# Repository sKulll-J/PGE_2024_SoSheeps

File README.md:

# PGE_2024_SoSheeps
Ce GitHub servira dans une première partie à regrouper les documentations, ressources utiles et notes en tous genres pour le PGE des SME 2024.

On sépareras les ressources dans des dossiers différents.

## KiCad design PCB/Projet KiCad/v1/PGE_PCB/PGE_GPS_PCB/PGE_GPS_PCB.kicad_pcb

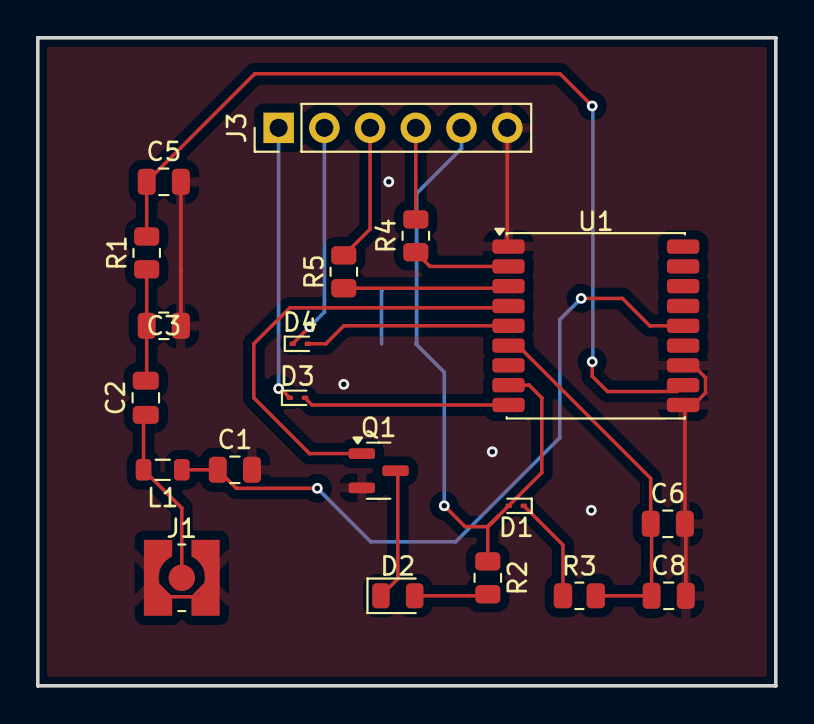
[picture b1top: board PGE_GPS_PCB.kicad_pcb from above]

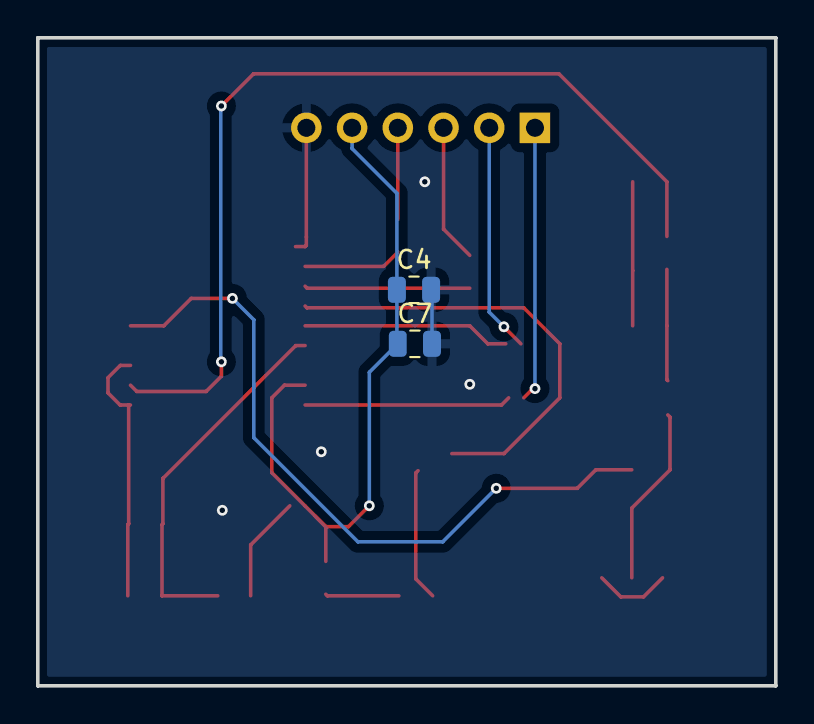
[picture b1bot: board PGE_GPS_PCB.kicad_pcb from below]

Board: 2 copper layers, 41.0 x 36.0 mm, 22 parts (2 on the bottom side), 19 nets.

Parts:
C1, C7, C8: 100nF; C_0805_2012Metric
C2: 100pF; C_0805_2012Metric
C3, C5: DNP_0805; C_0805_2012Metric
C4, C6: 4.7µF; C_0805_2012Metric
D1, D3, D4: RB521CM-30; D_SOD-923
D2: LED; LED_0805_2012Metric
J1: Antenne_GPS; WR-MMCX_Wuerth_66012102111404_Vertical
J3: Conn_01x06_Pin; PinHeader_1x06_P2.54mm_Vertical
L1: 47nH; L_0805_2012Metric
Q1: IRLML6244; SOT-23
R1: 0R; R_0805_2012Metric
R2: 330R; R_0805_2012Metric
R3: 1K; R_0805_2012Metric
R4, R5: 100R; R_0805_2012Metric
U1: L76-R; Quectel_L76

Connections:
1PPS: Q1.1 (G), U1.4 (1PPS)
GND: C1.2, C3.2, C4.2, C5.2, C6.2, C7.2, C8.2, J1.2 (Ext), J3.6, Q1.2 (S), U1.1 (GND), U1.10 (GND), U1.12 (GND)
GPS_RX: J3.3, R5.2
GPS_TX: J3.4, R4.2
GPS_reset: D3.1, J3.1
unnamed: C2.2, C3.1, R1.1
unnamed: D1.1, R3.1
unnamed: D2.2 (A), R2.2
unnamed: D2.1 (K), Q1.3 (D)
unnamed: D3.2 (A), U1.9 (~RESET)
unnamed: D4.2 (A), U1.5 (STANDBY)
unnamed: C2.1, J1.1 (In), L1.2
unnamed: R5.1, U1.3 (RXD1)
unnamed: R4.1, U1.2 (TXD1)
RF_IN: C5.1, R1.2, U1.11 (RF_IN)
VCC_RF: C1.1, L1.1, U1.14 (VCC_RF)
VDD_3.3V: C4.1, C7.1, D1.2 (A), J3.5, R2.1, U1.8 (VCC)
V_BCKP: C6.1, C8.1, R3.2, U1.6 (V_BCKP)
standby: D4.1, J3.2

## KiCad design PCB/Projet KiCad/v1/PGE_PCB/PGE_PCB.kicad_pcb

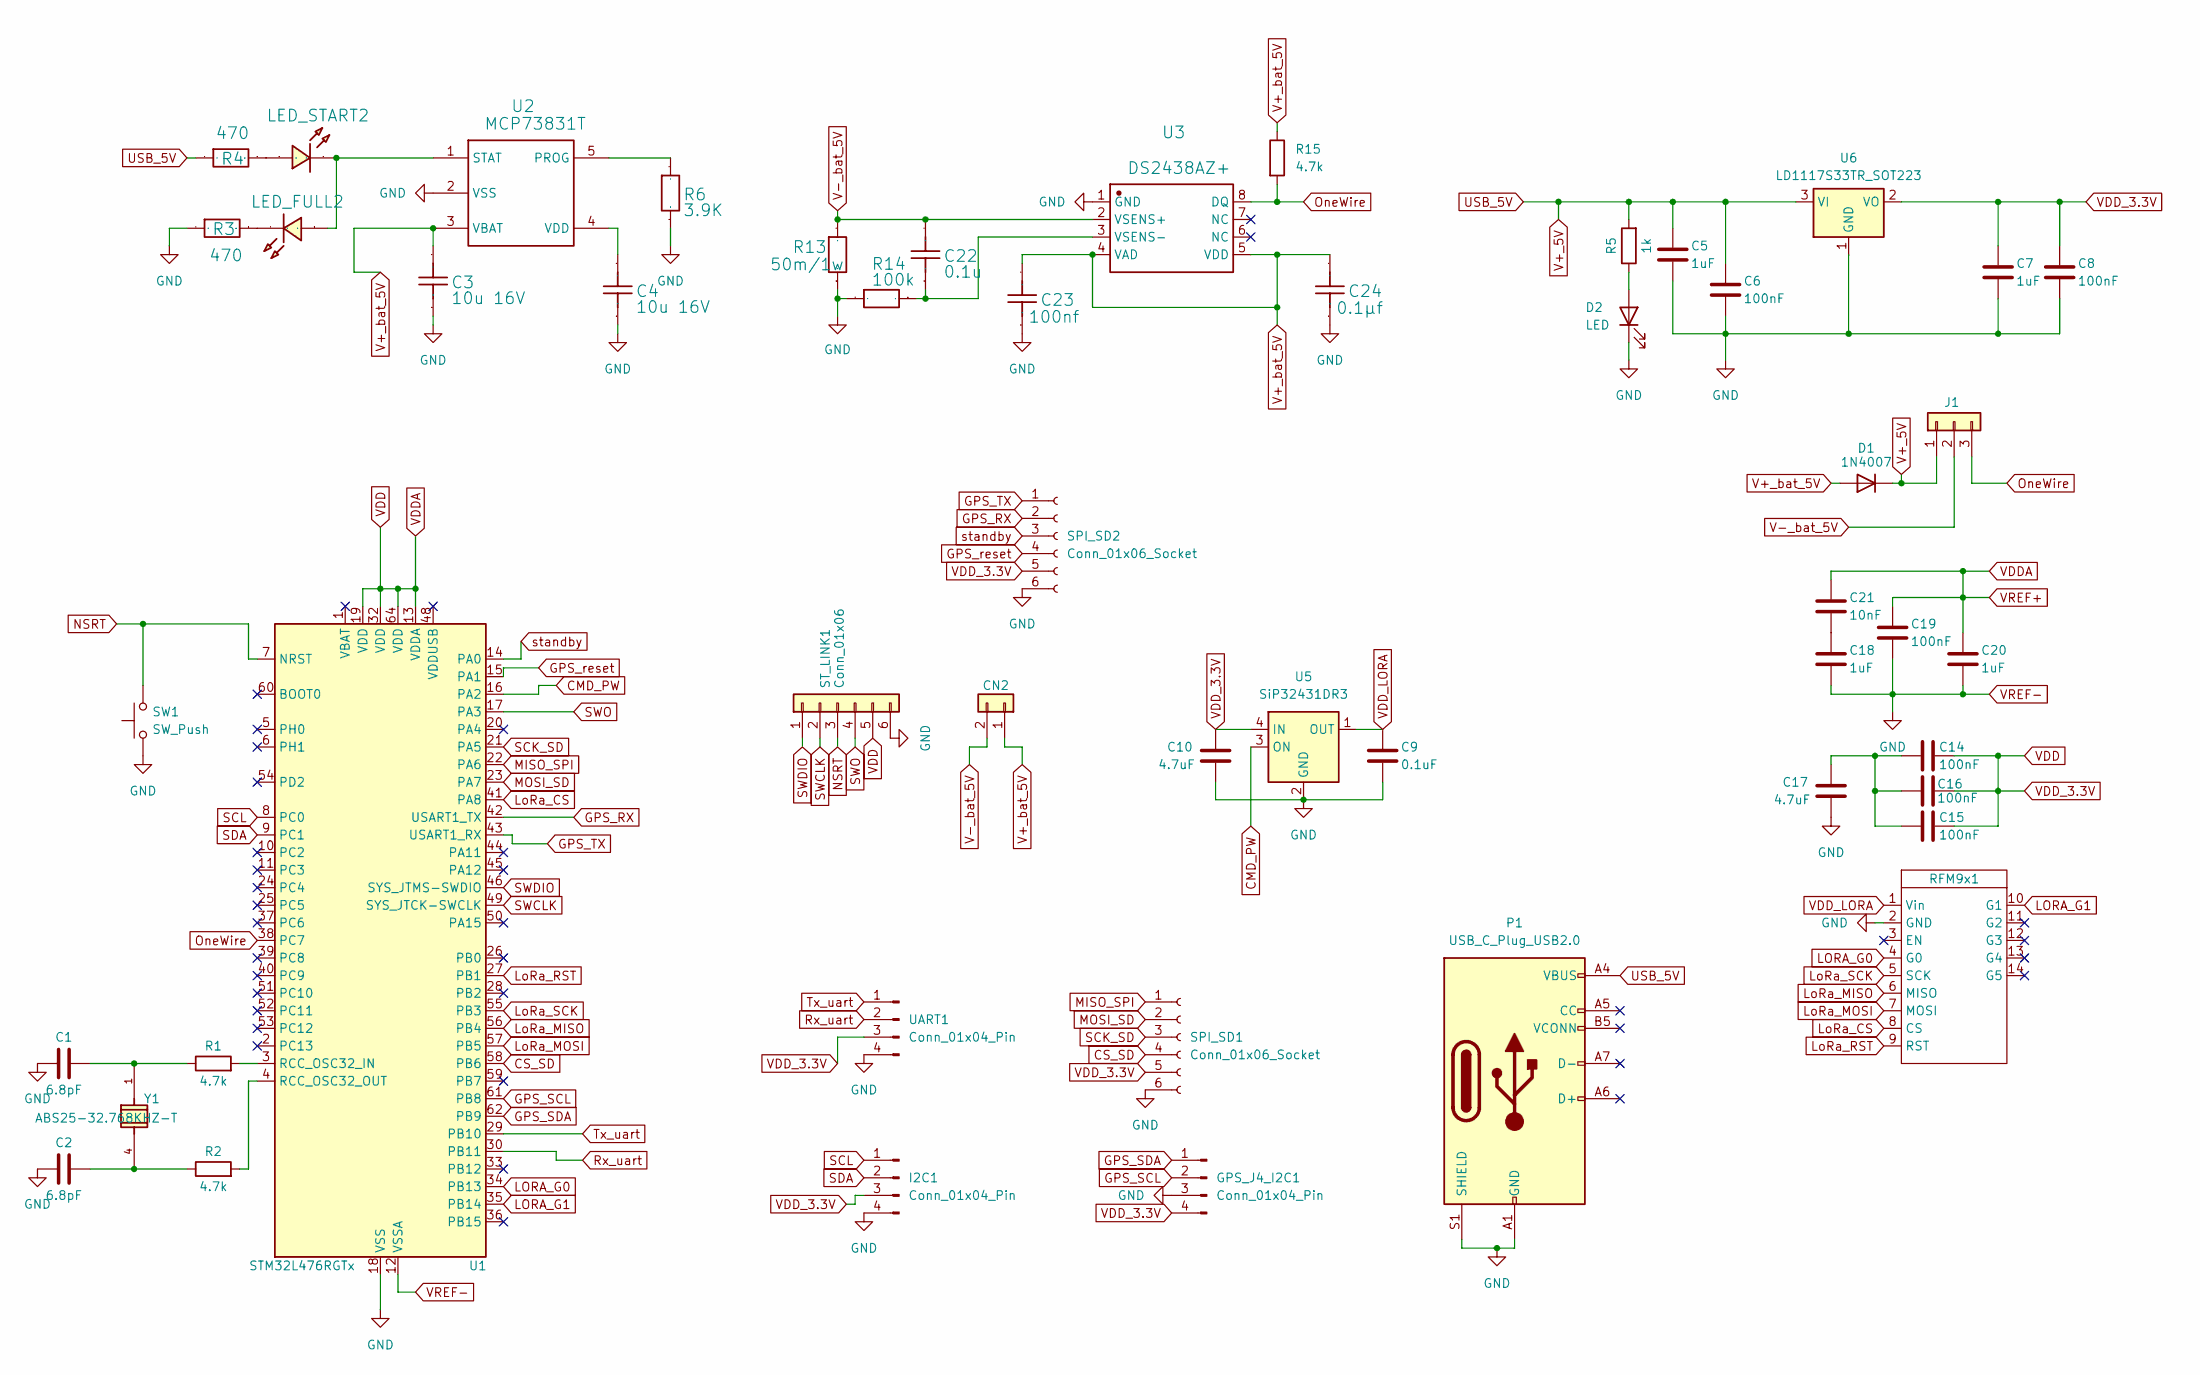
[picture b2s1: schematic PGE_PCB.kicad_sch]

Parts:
C1, C2: 6.8pF; C_0805_2012Metric
C3, C4: 10u 16V; C_0805_2012Metric
C5, C7, C18, C20: 1uF; C_0805_2012Metric
C6, C8, C14, C15, C16, C19: 100nF; C_0805_2012Metric
C9: 0.1uF; C_0805_2012Metric
C10, C17: 4.7uF; C_0805_2012Metric
C21: 10nF; C_0805_2012Metric
C22: 0.1u; C_0805_2012Metric
C23: 100nf; C_0805_2012Metric
C24: 0.1µf; C_0805_2012Metric
CN2: Conn_01x02; TerminalBlock_MetzConnect_Type011_RT05502HBWC_1x02_P5.00mm_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
D1: 1N4007; D_SMA
D2: LED; LED_0805_2012Metric
GPS_J4_I2C1: Conn_01x04_Pin; PinHeader_1x04_P2.54mm_Vertical
I2C1: Conn_01x04_Pin; PinHeader_1x04_P2.54mm_Vertical
J1: Conn_01x03; PinHeader_1x03_P2.54mm_Vertical
LED_FULL2: LED-0805_G; LED_0805_2012Metric
LED_START2: LED-0603_B; LED_0805_2012Metric
P1: USB_C_Plug_USB2.0; USB_C_Receptacle_Palconn_UTC16-G
R1, R2, R15: 4.7k; R_0805_2012Metric
R3, R4: 470; R_0805_2012Metric
R5: 1k; R_0805_2012Metric
R6: 3.9K; R_0805_2012Metric
R13: 50m/1w; R_0805_2012Metric
R14: 100k; R_0805_2012Metric
RFM9x1: LoRa_Breakout
SPI_SD1, SPI_SD2: Conn_01x06_Socket; PinHeader_1x06_P2.54mm_Vertical
ST_LINK1: Conn_01x06; JST_EH_B6B-EH-A_1x06_P2.50mm_Vertical
SW1: SW_Push; SW_SPST_CK_KMS2xxGP
U1: STM32L476RGTx; LQFP-64_10x10mm_P0.5mm
U2: MCP73831T; SOT-23-5
U3: DS2438AZ+; SOIC-8_3.9x4.9mm_P1.27mm
U5: SiP32431DR3; SOT-363_SC-70-6
U6: LD1117S33TR_SOT223; SOT-223-3_TabPin2
UART1: Conn_01x04_Pin; PinHeader_1x04_P2.54mm_Vertical
Y1: ABS25-32.768KHZ-T; XTAL_ABS25-32.768KHZ-6-1-T; PARTREV 12.01.15

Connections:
CMD_PW: U1.16 (PA2), U5.3 (ON)
CS_SD: SPI_SD1.4, U1.58 (PB6)
GPS_RX: SPI_SD2.2, U1.42 (USART1_TX)
GPS_SCL: GPS_J4_I2C1.2, U1.61 (PB8)
GPS_SDA: GPS_J4_I2C1.1, U1.62 (PB9)
GPS_TX: SPI_SD2.1, U1.43 (USART1_RX)
GPS_reset: SPI_SD2.4, U1.15 (PA1)
LORA_G0: RFM9x1.4 (G0), U1.34 (PB13)
LORA_G1: RFM9x1.10 (G1), U1.35 (PB14)
LoRa_CS: RFM9x1.8 (CS), U1.41 (PA8)
LoRa_MISO: RFM9x1.6 (MISO), U1.56 (PB4)
LoRa_MOSI: RFM9x1.7 (MOSI), U1.57 (PB5)
LoRa_RST: RFM9x1.9 (RST), U1.27 (PB1)
LoRa_SCK: RFM9x1.5 (SCK), U1.55 (PB3)
MISO_SPI: SPI_SD1.1, U1.22 (PA6)
MOSI_SD: SPI_SD1.2, U1.23 (PA7)
NSRT: ST_LINK1.3, SW1.2, U1.7 (NRST)
unnamed: C1.2, R1.1, Y1.1
unnamed: C2.2, R2.1, Y1.4
unnamed: C14.2, C15.2, C16.2, C17.1
unnamed: C18.1, C21.2
unnamed: D2.2 (A), R5.1
unnamed: LED_FULL2.2, R3.1
unnamed: LED_START2.1, R4.1
unnamed: R1.2, U1.3 (RCC_OSC32_IN)
unnamed: R2.2, U1.4 (RCC_OSC32_OUT)
unnamed: R6.2, U2.5 (PROG)
unnamed: LED_FULL2.1, LED_START2.2, U2.1 (STAT)
unnamed: C4.2, U2.4 (VDD)
unnamed: C22.1, R14.1, U3.3 (VSENS-)
OneWire: J1.3, R15.2, U1.38 (PC7), U3.8 (DQ)
Rx_uart: U1.30 (PB11), UART1.2
SCK_SD: SPI_SD1.3, U1.21 (PA5)
SCL: I2C1.1, U1.8 (PC0)
SDA: I2C1.2, U1.9 (PC1)
SWCLK: ST_LINK1.2, U1.49 (SYS_JTCK-SWCLK)
SWDIO: ST_LINK1.1, U1.46 (SYS_JTMS-SWDIO)
SWO: ST_LINK1.4, U1.17 (PA3)
Tx_uart: U1.29 (PB10), UART1.1
USB_5V: C5.1, C6.1, D1.1 (K), J1.1, P1.A4 (VBUS), P1.A9 (VBUS), P1.B4 (VBUS), P1.B9 (VBUS), R4.2, R5.2, U6.3 (VI)
V+_bat_5V: C3.2, C23.2, C24.2, CN2.1, D1.2 (A), R15.1, U2.3 (VBAT), U3.4 (VAD), U3.5 (VDD)
V-_bat_5V: C22.2, CN2.2, J1.2, R13.2, U3.2 (VSENS+)
VDD: C7.1, C8.1, C10.1, C14.1, C15.1, C16.1, C19.1, C20.1, C21.1, GPS_J4_I2C1.4, I2C1.3, SPI_SD1.5, SPI_SD2.5, ST_LINK1.5, U1.13 (VDDA), U1.19 (VDD), U1.32 (VDD), U1.64 (VDD), U5.4 (IN), U6.2 (VO), UART1.3
VDD_LORA: C9.1, RFM9x1.1 (Vin), U5.1 (OUT)
VREF-: C1.1, C2.1, C3.1, C4.1, C5.2, C6.2, C7.2, C8.2, C9.2, C10.2, C17.2, C18.2, C19.2, C20.2, C23.1, C24.1, D2.1 (K), GPS_J4_I2C1.3, I2C1.4, P1.A1 (GND), P1.A12 (GND), P1.B1 (GND), P1.B12 (GND), P1.S1 (SHIELD), R3.2, R6.1, R13.1, R14.2, RFM9x1.2 (GND), SPI_SD1.6, SPI_SD2.6, ST_LINK1.6, SW1.1, U1.12 (VSSA), U1.18 (VSS), U1.31 (VSS), U1.47 (VSS), U1.63 (VSS), U2.2 (VSS), U3.1 (GND), U5.2 (GND), U5.5 (GND), U6.1 (GND), UART1.4
standby: SPI_SD2.3, U1.14 (PA0)

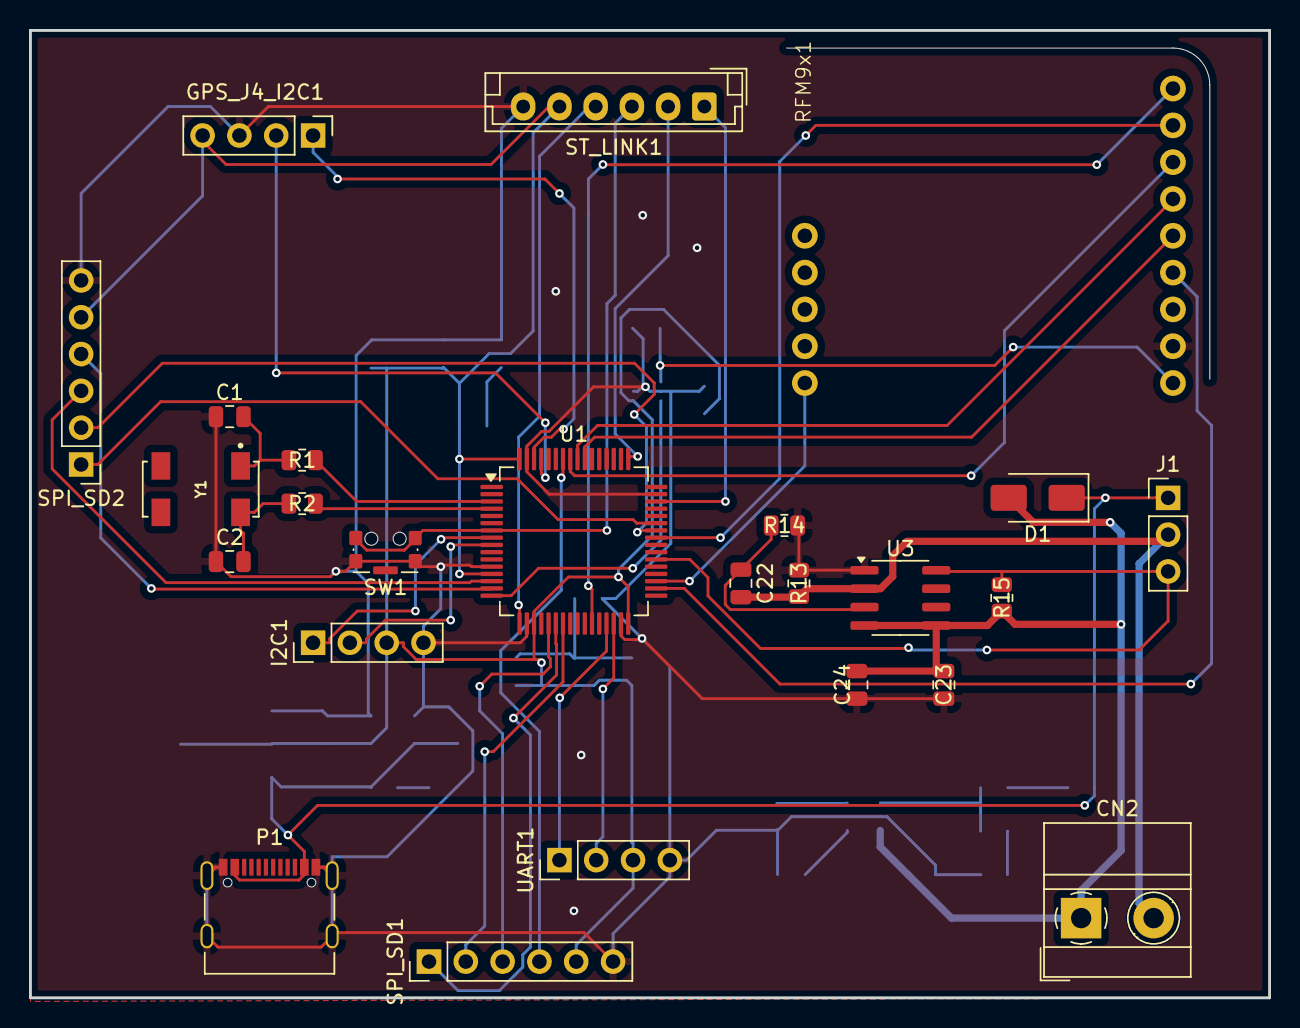
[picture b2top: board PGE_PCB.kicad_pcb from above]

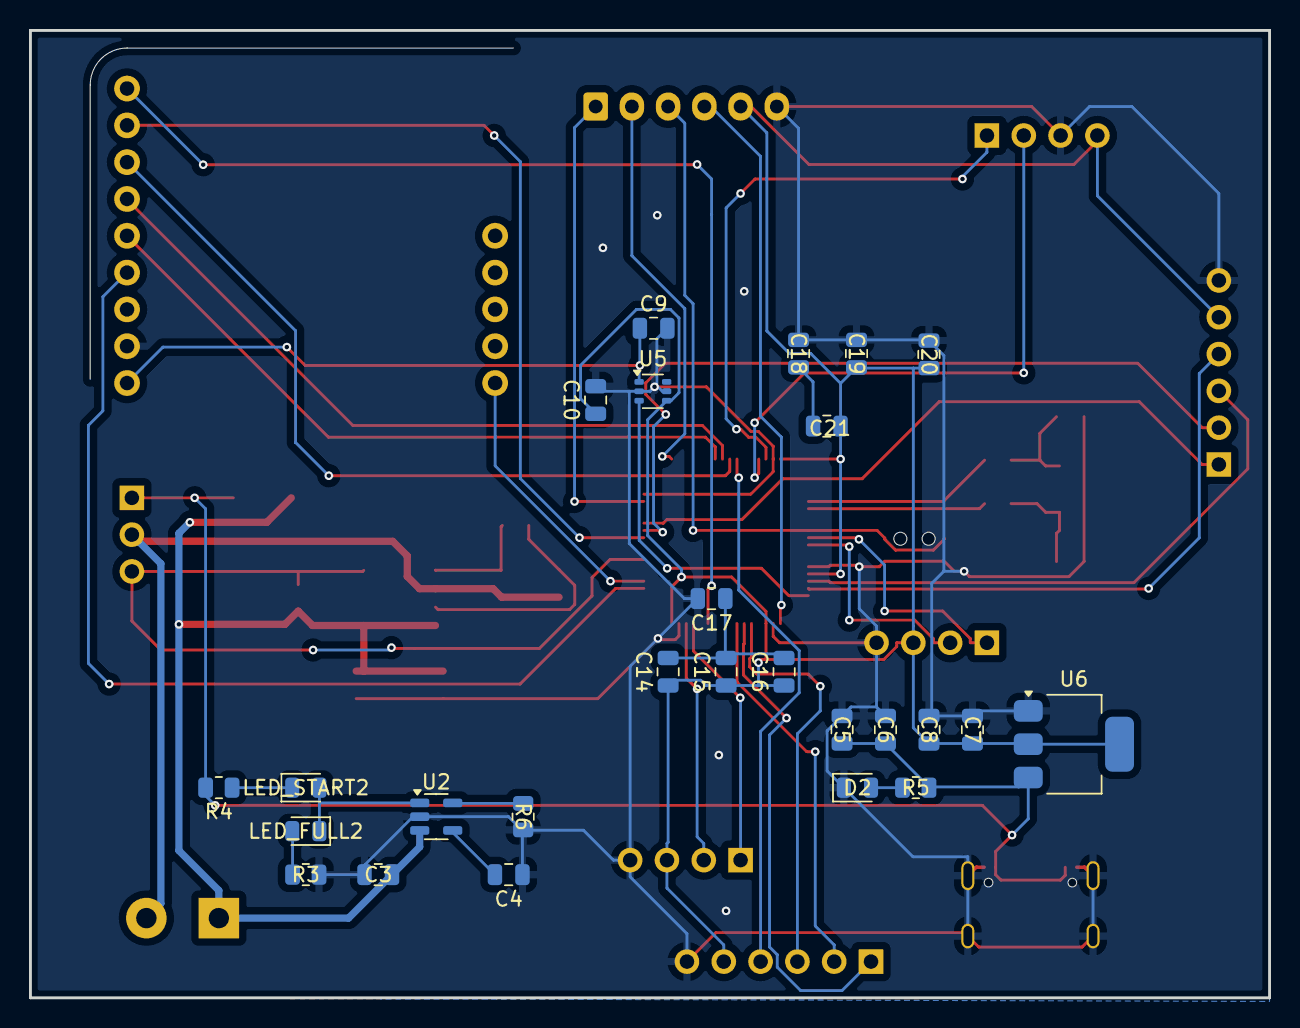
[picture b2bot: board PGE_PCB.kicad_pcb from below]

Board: 2 copper layers, 85.5 x 66.8 mm, 51 parts (26 on the bottom side), 46 nets.

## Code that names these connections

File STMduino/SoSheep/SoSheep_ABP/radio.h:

#pragma once

#include <RadioLib.h>
#include "LoRaWAN.h"

// RFM9x pin configuration
#define MOSI_PIN  PB5  
#define MISO_PIN  PB4   
#define SCLK_PIN  PB3   

#define CS_PIN    PA8   
#define RST_PIN   PB1

#define G0_PIN    PB13
#define G1_PIN    PB14

// result code to text - these are error codes that can be raised when using LoRaWAN
// however, RadioLib has many more - see https://jgromes.github.io/RadioLib/group__status__codes.html for a complete list
String stateDecode(const int16_t result);

// helper function to display any issues
void debug(bool failed, const __FlashStringHelper* message, int state, bool halt);

// helper function to display a byte array
void arrayDump(uint8_t *buffer, uint16_t len);

// initialization function in setup()
void radio_init(SPIClass etx_spi, SPISettings spi_Settings, SX1276 radio, LoRaWANNode node );

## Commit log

2024-09-25 README.md
2024-11-22 Main commit
2024-12-18 Creation du projet KiCad Ajout git ignore, ajout projet KiCad v1, ajout dossier datasheet Kristen
2024-12-19 Modification Schéma PCB (19/12) -Ajout Module alimentation -Ajout Module GPS -Ajout Port USB Kristen
2025-01-07 Ajout sous-feuille Alimentation
2025-01-13 Ajout d'une resistance de pullup sur la ligne OneWire
2025-01-16 RFM96W LoRaWAN template
2025-01-16 Algorithme de ray casting
2025-01-16 Maj PCB
    - correction module GPS (I2C)
    - ajout module LoRa RFM9x
2025-01-16 Modifications UC : Éditer champs
2025-01-17 Correction UC Éditer zones
2025-01-20 Update Sysml
2025-01-23 Update gitignore
2025-01-24 mise à jour Kicad
2025-01-24 fin routage prototype_V1
    Pour avis Kristen
2025-01-27 Update LoRaWAN join tests
2025-01-28 Update
    - IBD Sysml
    - minor change on OTAA join test
2025-01-28 Appli_Mobile.zip
2025-01-28 Update configABP.h
    fixed wrong FNWKSINT Key
2025-01-28 PCB_Proto_PGE Terminé
2025-01-28 Update PCB
2025-01-29 Ajout Code BMS
2025-01-31 Reorganizing
2025-02-03 cleanup
2025-02-03 Update LoRaWAN
    -collars
2025-02-06 update OTAA
2025-02-10 Code pour la lecture SOC avec la méthode tension
2025-02-11 Pcb VERSION GPS séparer
2025-02-12 upload full code
    BMS + GPS + Radio
2025-02-13 kiCad gitignore
2025-02-13 upload
    code test timestamps
2025-02-14 Fix payload build function
    should put the coordinates correctly now
2025-02-19 deplaced payload build function into radio.h
2025-02-20 Reorganize code
2025-02-20 Code BMS adapté selon les mesures faites de la courbe de decharge
2025-02-21 added get Num Sat function
2025-02-21 fix variables names
2025-02-28 Create Application_Mobile
2025-02-28 Ajout du dossier Application Mobile
2025-02-28 Supprimer des dossiers Application Mobile
2025-03-03 3D models
2026-01-16 Main maj - stage
2026-01-16 apk build
